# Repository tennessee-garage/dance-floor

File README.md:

# dance-floor
Code for various components of the LED disco dance floor

* [eagle](https://github.com/garthwebb/dance-floor/tree/master/eagle) - Eagle files for the PCBs used in this project
* [floor](https://github.com/garthwebb/dance-floor/tree/master/floor) - This code controls the light show on the dance floor
* poc_test - Proof of concept test code.
* [spi-buffer](https://github.com/garthwebb/dance-floor/tree/master/spi-buffer) - This code handles reading SPI weight data coming from the floor
* [square](https://github.com/garthwebb/dance-floor/tree/master/square) - This code run on the ATTiny in each square and manages the lights and weight sensors

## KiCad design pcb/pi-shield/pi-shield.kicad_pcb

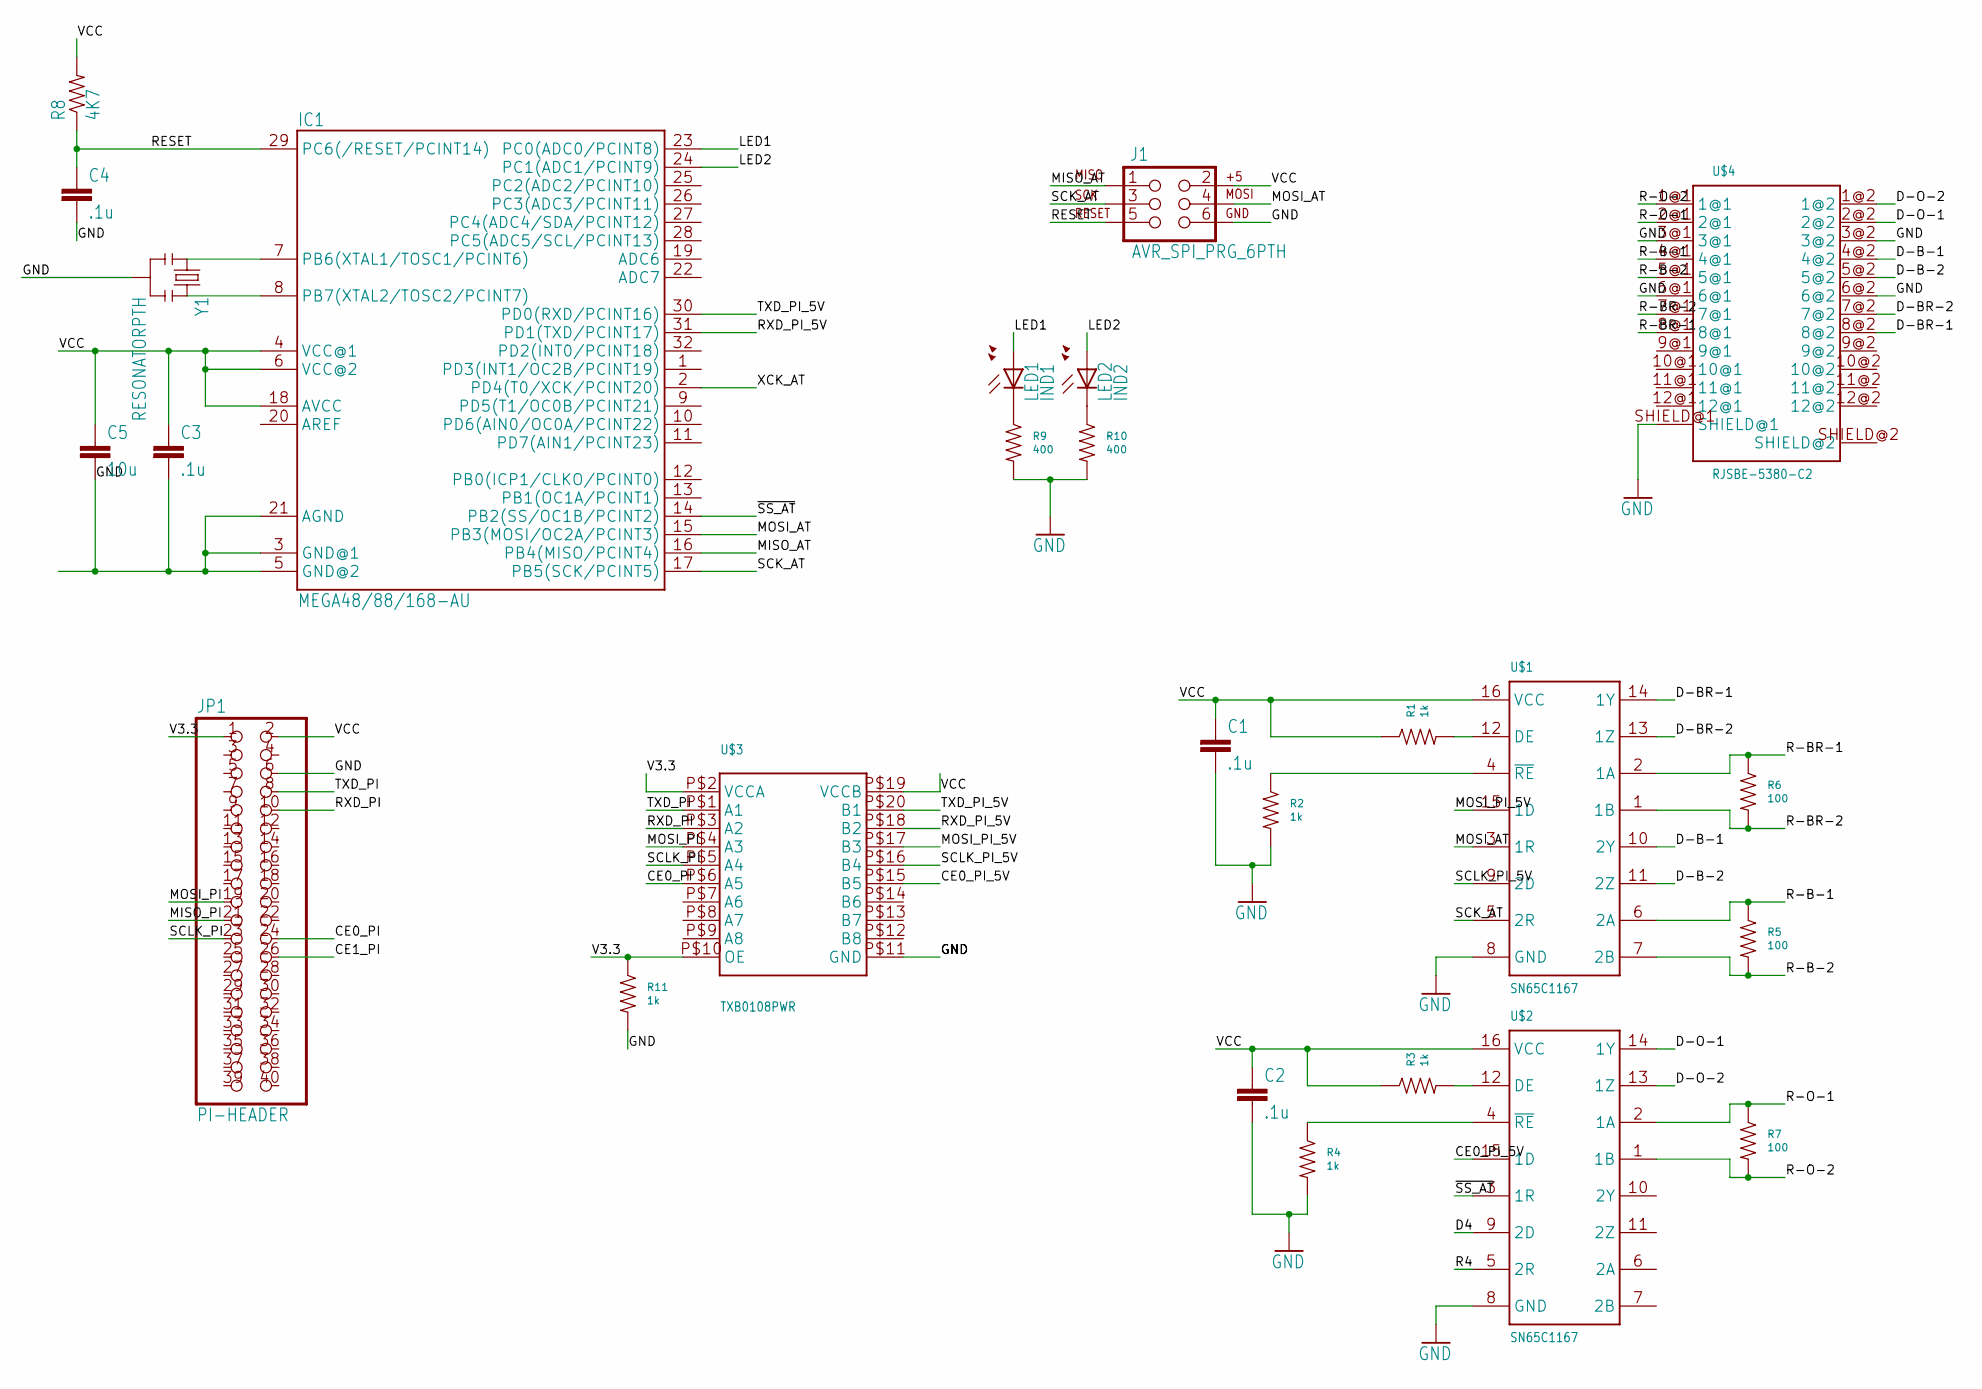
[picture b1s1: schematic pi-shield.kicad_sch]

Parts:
C1, C2, C3, C4: .1u; 0805
C5: 10u; 0805
IC1: MEGA48/88/168-AU; TQFP32-08
J1: AVR_SPI_PRG_6PTH; 2X3
JP1: PI-HEADER; 2X20
LED1: IND1; LED3MM
LED2: IND2; LED3MM
R1, R2, R3, R4, R11: 1k; R0805
R5, R6, R7: 100; R0805
R8: 4K7; 0805
R9, R10: 400; R0805
U$1, U$2: SN65C1167; SOP-16
U$3: TXB0108PWR; TSSOP20
U$4: RJSBE-5380-C2
Y1: RESONATORPTH; RESONATOR-PTH

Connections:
CE0_PI: JP1.24, U$3.P$6 (A5)
CE0_PI_5V: U$2.15 (1D), U$3.P$15 (B5)
CE1_PI: JP1.26
D4: U$2.9 (2D)
D-B-1: U$1.10 (2Y), U$4.4@2
D-B-2: U$1.11 (2Z), U$4.5@2
D-BR-1: U$1.14 (1Y), U$4.8@2
D-BR-2: U$1.13 (1Z), U$4.7@2
D-O-1: U$2.14 (1Y), U$4.2@2
D-O-2: U$2.13 (1Z), U$4.1@2
GND: C1.2, C2.2, C3.2, C4.2, C5.2, IC1.3 (GND@1), IC1.5 (GND@2), IC1.21 (AGND), J1.6, JP1.6, R2.P$2, R4.P$2, R9.P$2, R10.P$2, R11.P$2, U$1.8 (GND), U$2.8 (GND), U$3.P$11 (GND), U$4.3@1, U$4.3@2, U$4.6@1, U$4.6@2, U$4.SHIELD@1, Y1.2
LED1: IC1.23 (PC0(ADC0/PCINT8)), LED1.A
LED2: IC1.24 (PC1(ADC1/PCINT9)), LED2.A
MISO_AT: IC1.16 (PB4(MISO/PCINT4)), J1.1
MISO_PI: JP1.21
MOSI_AT: IC1.15 (PB3(MOSI/OC2A/PCINT3)), J1.4, U$1.3 (1R)
MOSI_PI: JP1.19, U$3.P$4 (A3)
MOSI_PI_5V: U$1.15 (1D), U$3.P$17 (B3)
unnamed: R1.P$2, U$1.12 (DE)
unnamed: R2.P$1, U$1.4 (~RE)
unnamed: R3.P$2, U$2.12 (DE)
unnamed: R4.P$1, U$2.4 (~RE)
unnamed: LED1.K (C), R9.P$1
unnamed: LED2.K (C), R10.P$1
unnamed: IC1.7 (PB6(XTAL1/TOSC1/PCINT6)), Y1.1
unnamed: IC1.8 (PB7(XTAL2/TOSC2/PCINT7)), Y1.3
R4: U$2.5 (2R)
R-B-1: R5.P$1, U$1.6 (2A), U$4.4@1
R-B-2: R5.P$2, U$1.7 (2B), U$4.5@1
R-BR-1: R6.P$1, U$1.2 (1A), U$4.8@1
R-BR-2: R6.P$2, U$1.1 (1B), U$4.7@1
R-O-1: R7.P$1, U$2.2 (1A), U$4.2@1
R-O-2: R7.P$2, U$2.1 (1B), U$4.1@1
RESET: C4.1, IC1.29 (PC6(/RESET/PCINT14)), J1.5, R8.1
RXD_PI: JP1.10, U$3.P$3 (A2)
RXD_PI_5V: IC1.31 (PD1(TXD/PCINT17)), U$3.P$18 (B2)
SCK_AT: IC1.17 (PB5(SCK/PCINT5)), J1.3, U$1.5 (2R)
SCLK_PI: JP1.23, U$3.P$5 (A4)
SCLK_PI_5V: U$1.9 (2D), U$3.P$16 (B4)
TXD_PI: JP1.8, U$3.P$1 (A1)
TXD_PI_5V: IC1.30 (PD0(RXD/PCINT16)), U$3.P$20 (B1)
V3.3: JP1.1, R11.P$1, U$3.P$2 (VCCA), U$3.P$10 (OE)
VCC: C1.1, C2.1, C3.1, C5.1, IC1.4 (VCC@1), IC1.6 (VCC@2), IC1.18 (AVCC), J1.2, JP1.2, R1.P$1, R3.P$1, R8.2, U$1.16 (VCC), U$2.16 (VCC), U$3.P$19 (VCCB)
XCK_AT: IC1.2 (PD4(T0/XCK/PCINT20))
~SS_AT: IC1.14 (PB2(SS/OC1B/PCINT2)), U$2.3 (1R)

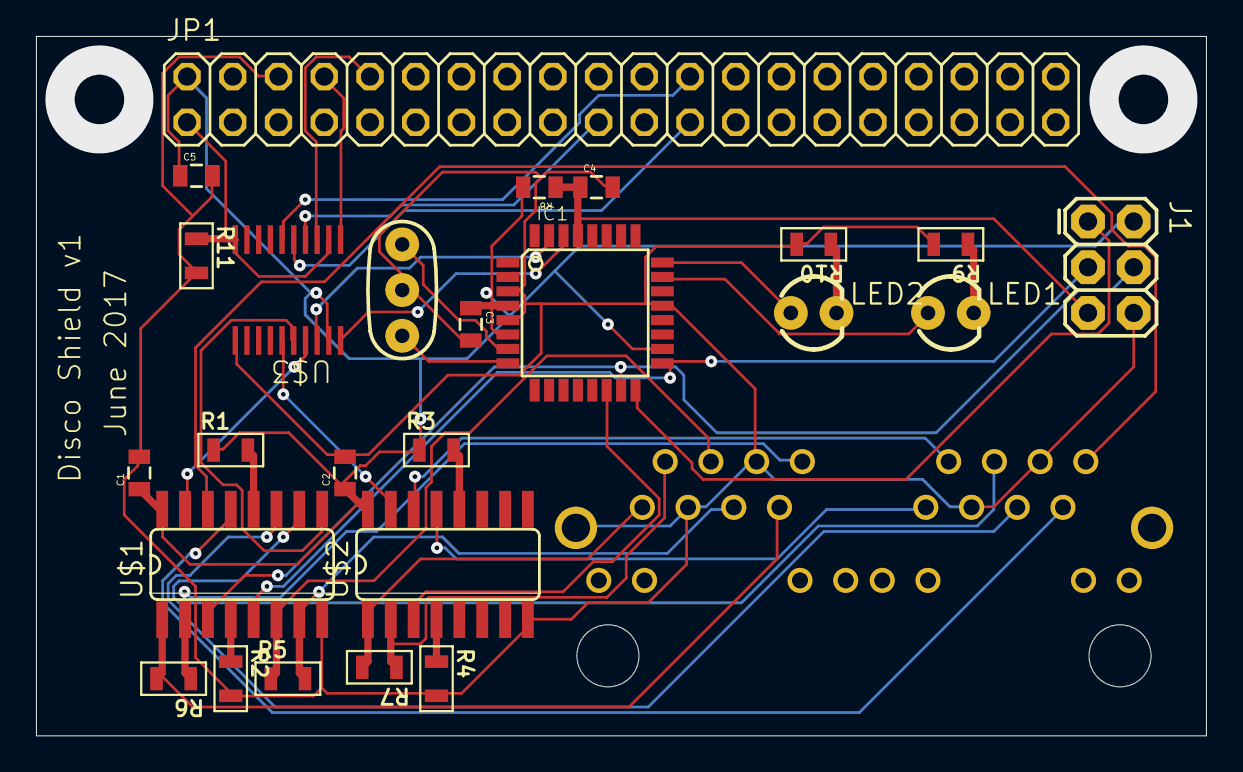
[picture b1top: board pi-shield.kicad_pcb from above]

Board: 2 copper layers, 65.0 x 38.9 mm, 26 parts (0 on the bottom side), 40 nets.

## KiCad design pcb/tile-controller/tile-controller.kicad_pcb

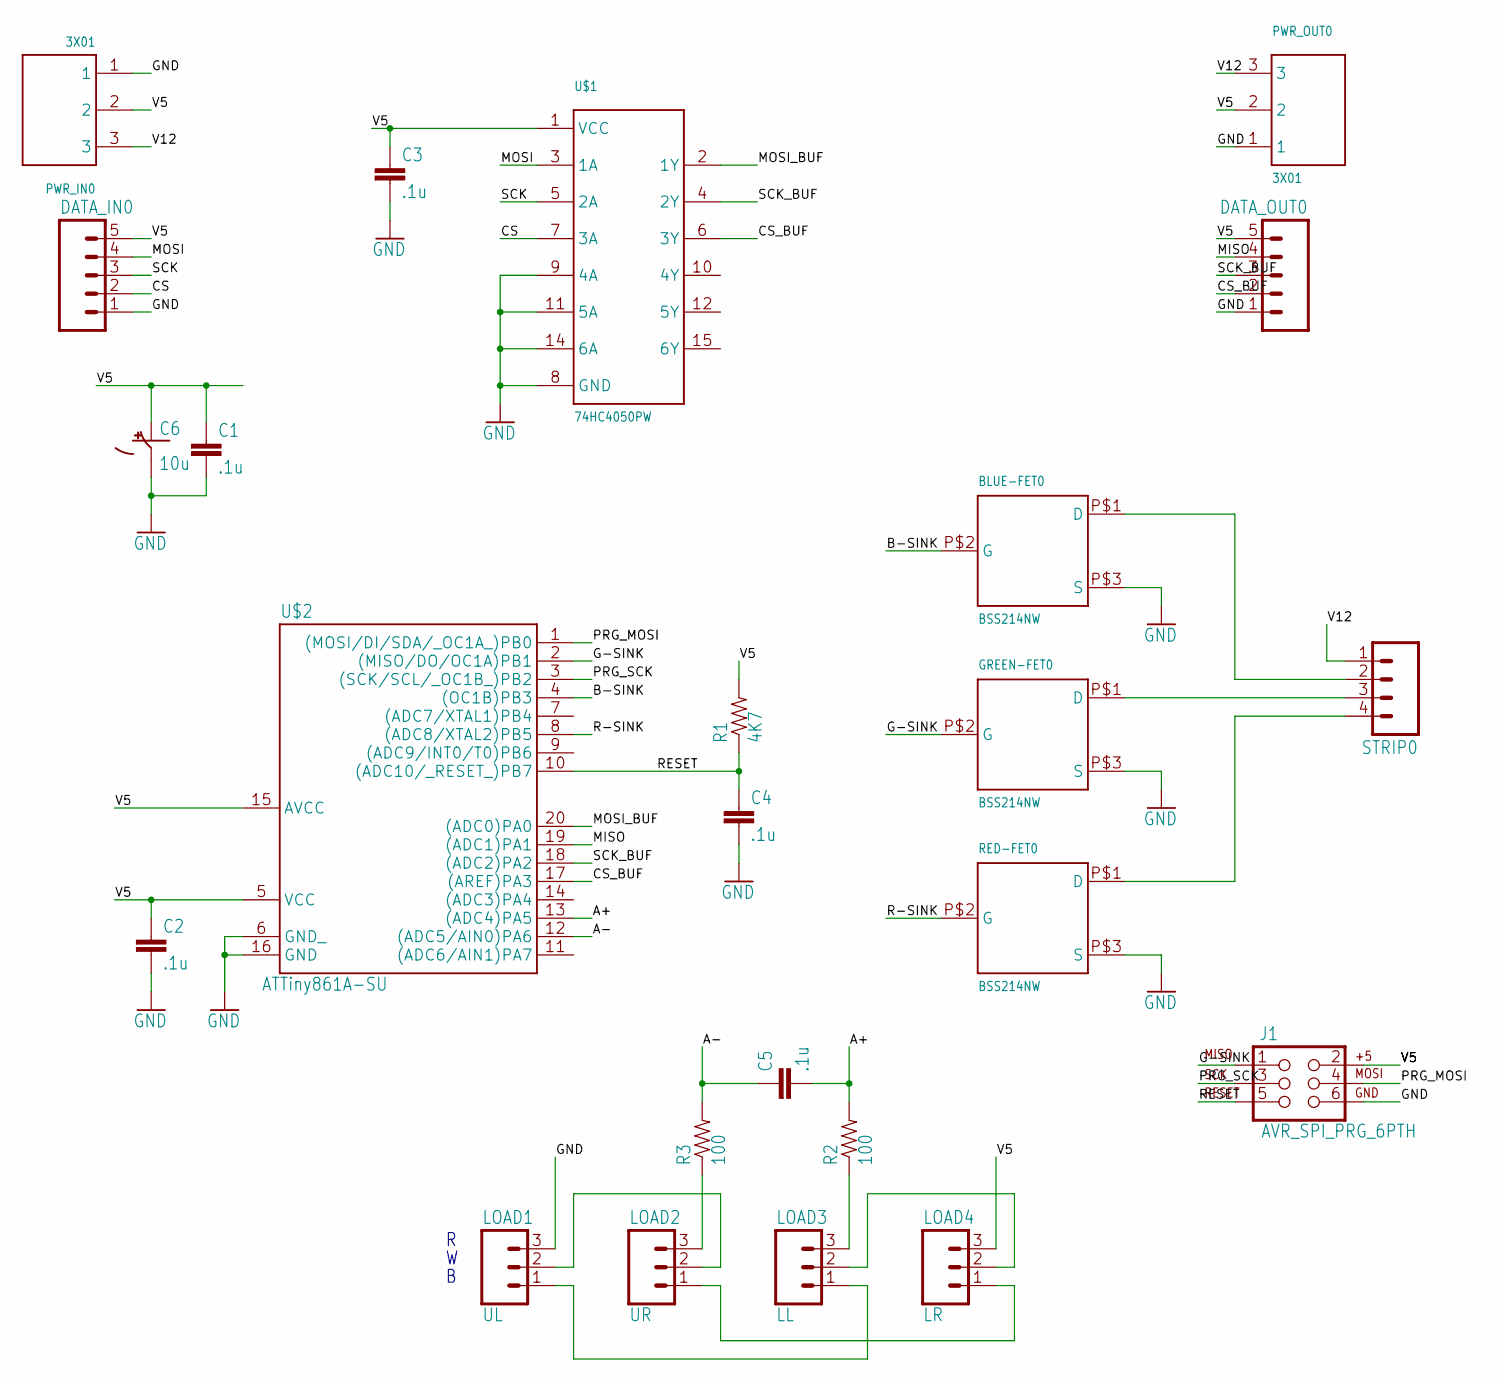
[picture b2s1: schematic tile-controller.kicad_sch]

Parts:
BLUE-FET0: BSS214NW; SOT-323
C1, C2, C3, C4, C5: .1u; 0805
C6: 10u; EIA3216
DATA_IN0: M05PTH; 1X05
DATA_OUT0: M05PTH; 1X05
GREEN-FET0: BSS214NW; SOT-323
J1: AVR_SPI_PRG_6PTH; 2X3
LOAD1: UL; 1X03
LOAD2: UR; 1X03
LOAD3: LL; 1X03
LOAD4: LR; 1X03
PWR_IN0: 3X01; 3X01-18AWG
PWR_OUT0: 3X01; 3X01-18AWG
R1: 4K7; 0805
R2, R3: 100; 0805
RED-FET0: BSS214NW; SOT-323
STRIP0: M04PTH; 1X04
U$1: 74HC4050PW; TSSOP16.2
U$2: ATTiny861A-SU; SO20L$

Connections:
A+: C5.2, R2.2, U$2.13 ((ADC4)PA5)
A-: C5.1, R3.2, U$2.12 ((ADC5/AIN0)PA6)
B-SINK: BLUE-FET0.P$2 (G), U$2.4 ((OC1B)PB3)
CS: DATA_IN0.2, U$1.7 (3A)
CS_BUF: DATA_OUT0.2, U$1.6 (3Y), U$2.17 ((AREF)PA3)
G-SINK: GREEN-FET0.P$2 (G), J1.1, U$2.2 ((MISO/DO/OC1A)PB1)
GND: BLUE-FET0.P$3 (S), C1.2, C2.2, C3.2, C4.2, C6.C (-), DATA_IN0.1, DATA_OUT0.1, GREEN-FET0.P$3 (S), J1.6, LOAD1.3, PWR_IN0.1, PWR_OUT0.1, RED-FET0.P$3 (S), U$1.8 (GND), U$1.9 (4A), U$1.11 (5A), U$1.14 (6A), U$2.6 (GND_), U$2.16 (GND)
MISO: DATA_OUT0.4, U$2.19 ((ADC1)PA1)
MOSI: DATA_IN0.4, U$1.3 (1A)
MOSI_BUF: U$1.2 (1Y), U$2.20 ((ADC0)PA0)
unnamed: LOAD1.1, LOAD3.1
unnamed: LOAD2.1, LOAD4.1
unnamed: GREEN-FET0.P$1 (D), STRIP0.3
unnamed: BLUE-FET0.P$1 (D), STRIP0.2
unnamed: RED-FET0.P$1 (D), STRIP0.4
unnamed: LOAD1.2, LOAD2.2
unnamed: LOAD3.2, LOAD4.2
PRG_MOSI: J1.4, U$2.1 ((MOSI/DI/SDA/_OC1A_)PB0)
PRG_SCK: J1.3, U$2.3 ((SCK/SCL/_OC1B_)PB2)
R-SINK: RED-FET0.P$2 (G), U$2.8 ((ADC8/XTAL2)PB5)
RESET: C4.1, J1.5, R1.1, U$2.10 ((ADC10/_RESET_)PB7)
SCK: DATA_IN0.3, U$1.5 (2A)
SCK_BUF: DATA_OUT0.3, U$1.4 (2Y), U$2.18 ((ADC2)PA2)
V5: C1.1, C2.1, C3.1, C6.A (+), DATA_IN0.5, DATA_OUT0.5, J1.2, LOAD4.3, PWR_IN0.2, PWR_OUT0.2, R1.2, U$1.1 (VCC), U$2.5 (VCC), U$2.15 (AVCC)
V12: PWR_IN0.3, PWR_OUT0.3, STRIP0.1
_1: LOAD2.3, R3.1
_2: LOAD3.3, R2.1

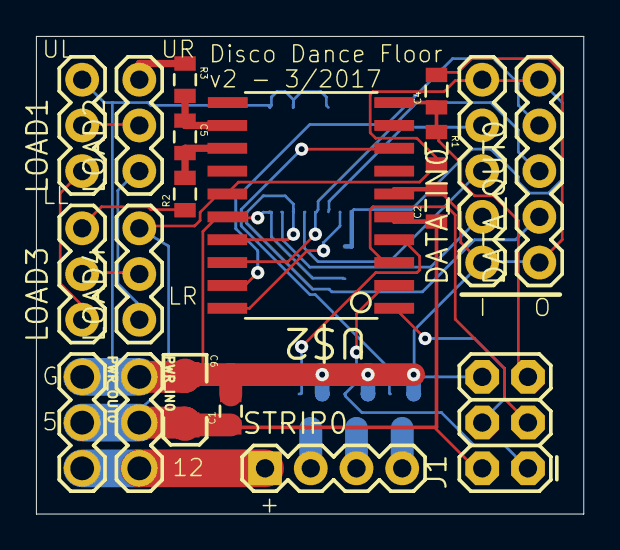
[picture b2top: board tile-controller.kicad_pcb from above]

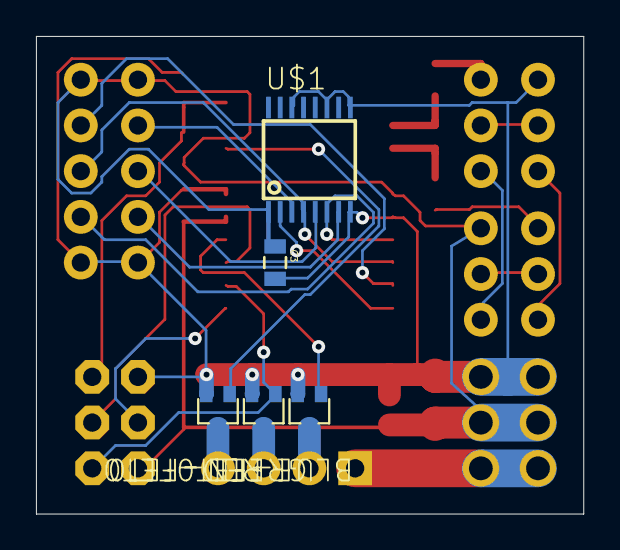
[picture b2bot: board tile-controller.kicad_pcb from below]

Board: 2 copper layers, 30.4 x 26.5 mm, 24 parts (5 on the bottom side), 27 nets.

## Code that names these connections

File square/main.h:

#ifndef _MAIN_H
#define _MAIN_H

#define SET_PA0() SET_PIN(PORTA, PA0)
#define SET_PA1() SET_PIN(PORTA, PA1)
#define SET_PA2() SET_PIN(PORTA, PA2)
#define SET_PA3() SET_PIN(PORTA, PA3)
#define SET_PA4() SET_PIN(PORTA, PA4)
#define SET_PA5() SET_PIN(PORTA, PA5)
#define SET_PA6() SET_PIN(PORTA, PA6)
#define SET_PA7() SET_PIN(PORTA, PA7)
#define CLEAR_PA0() CLEAR_PIN(PORTA, PA0)
#define CLEAR_PA1() CLEAR_PIN(PORTA, PA1)
#define CLEAR_PA2() CLEAR_PIN(PORTA, PA2)
#define CLEAR_PA3() CLEAR_PIN(PORTA, PA3)
#define CLEAR_PA4() CLEAR_PIN(PORTA, PA4)
#define CLEAR_PA5() CLEAR_PIN(PORTA, PA5)
#define CLEAR_PA6() CLEAR_PIN(PORTA, PA6)
#define CLEAR_PA7() CLEAR_PIN(PORTA, PA7)

#define SET_PB0() SET_PIN(PORTB, PB0)
#define SET_PB1() SET_PIN(PORTB, PB1)
#define SET_PB2() SET_PIN(PORTB, PB2)
#define SET_PB3() SET_PIN(PORTB, PB3)
#define SET_PB4() SET_PIN(PORTB, PB4)
#define SET_PB5() SET_PIN(PORTB, PB5)
#define SET_PB6() SET_PIN(PORTB, PB6)
#define SET_PB7() SET_PIN(PORTB, PB7)
#define CLEAR_PB0() CLEAR_PIN(PORTB, PB0)
#define CLEAR_PB1() CLEAR_PIN(PORTB, PB1)
#define CLEAR_PB2() CLEAR_PIN(PORTB, PB2)
#define CLEAR_PB3() CLEAR_PIN(PORTB, PB3)
#define CLEAR_PB4() CLEAR_PIN(PORTB, PB4)
#define CLEAR_PB5() CLEAR_PIN(PORTB, PB5)
#define CLEAR_PB6() CLEAR_PIN(PORTB, PB6)
#define CLEAR_PB7() CLEAR_PIN(PORTB, PB7)

#define SET_PIN(port, pin) port |= _BV(pin)
#define CLEAR_PIN(port, pin) port &= ~_BV(pin)

void init_avr(void);
void init_pwm(void);
void init_adc(void);
void set_red(uint16_t val);
void set_green(uint16_t val);
void set_blue(uint16_t val);
void handle_spi(void);
void handle_adc(void);
int main(void);

#endif

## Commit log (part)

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2017-02-03 More ignored files
2017-02-03 Code to measure differential ADC and light the lights according to the result
2017-02-26 Got i2c working (but buggy) and cleaned up code a bit
2017-03-28 A bit more clean up
2017-04-03 Storing all bytes in a long buffer. Considered using a 4 byte FIFO but keeping everying in one array is much simpler and the space is available.
2017-05-30 Start of the code for the SPI buffer
2017-05-31 Don't make this complicated
2017-06-01 Test program
2017-06-04 Get rid of *.pyc files from commits
2017-06-05 Added a message file that will be read, with default. Added color cycling
2017-06-05 add multiple sources, tweak decay time
2017-06-06 code cleanup
2017-06-08 add x,y args to build_mine
2017-06-10 Renamed the effect
2017-06-11 Updates to add keyboard input for weight values. Default is on. Can be turned off via:
    --no-opc-input
2017-06-12 Ignore DS_Store files
2017-06-12 Two new screenshots
2017-06-18 Additional board
2017-07-05 Don't track lock files
2017-07-09 Don't need to follow the OPC quickstart guide
2017-07-09 function to translate (x,y) coords to array index
2017-07-09 drop debug prints
2017-07-09 typo
2017-07-10 Added the radiating animation
2017-07-10 Unify the color functions in color_tools to the color_utils file
2017-07-10 Updated for PEP8
2017-07-20 Got the spi buffer streaming data via the USART
2017-07-20 use color_utils
2017-07-23 floor: devserver: simple support for weights onClick.
2017-07-23 floor: deserver: bugfix: handle non-integer rgb values.
2017-07-23 controller: bugfix.
2017-07-23 Initial API service.
2017-07-23 controller: support reloading processor modules.
2017-07-24 api: support `POST /api/bpm/nudge` (relative changes to bpm/downbeat).
2017-07-24 api: add `/api/status`, composite playlist and tempo info.
2017-07-25 Hyperspace
    added hyperspace processor, also added fishies and hyperspace to the playlist and added a color to rainbow_bunny
2017-07-27 Output the driver name and its max led value on start up
2017-07-28 Update the SPI buffer to only send the two bytes of weight information, rather than pass along the full four bytes it gets from the floor.
    Two of the four bytes will always be zero, so there's no need to transmit them. Since the two bytes represent a
    10-bit value, only 10 of the 16 bits in those two bytes are used, so we still have a valid stop condition (0xFF, 0xFF)
    Finally, handle serial synchronously rather than running a thread. Running a thread seemed to cause problems and made things more
    complex to program and debug. Its main goal was to make sure we weren't blocked on IO when we could be rendering a frame but that
    doesn't seem to be an issue.
2017-07-28 Some updates to deprecate OPC
2017-07-28 Add a time remaining indicator
2017-07-30 Make some improvements to electricity, though still not operating as well as I'd like
    Also make sure we don't get a warning when starting stripes
2017-07-30 api: add available processors to status API; docs.
2017-07-30 Add throbber to default playlist.
2017-08-03 api: add `POST /api/playlist/previous` to go back.
2017-08-05 Add "zap" to default playlist.
2017-10-15 Removed most references to the opc driver
    The OPC driver has been superseded by the devserver which is way better.
2018-04-26 Test with normal ADC and no odd off by 3 first frame from SPI
    Got this all working. Checkpointing
2018-08-26 Don't call data_ready as if its a function
2018-08-26 Refactor JS and CSS out a bit. Create page container
2018-08-26 Make sure the server doesn't die if the floor is powered on after the server is running.
2018-08-31 Add pipenv.
2018-09-17 tests: add unittest for the `clocked` decorator.
2018-09-18 Update to latest pymidi.
2018-09-18 Committing change to this file though it was probably just a perspective change /shrug
2018-09-20 midi: improve mapping support; add passthrough; add tests.
2018-09-21 Updated the playlist and added an alias for run show
2018-09-30 Append takes no args
2018-09-30 Update imports across project.
    * Add floor. to imports where necessary
    * Change ordering of imports to list global imports first, project local second.
    * Fix any PEP warnings
2018-10-01 Ok, default isn't a key
2018-10-01 Use an absolute path for the playlist.
    Otherwise where you start the script matters
2018-10-01 Fix dynamic import
2018-10-14 Allow patterns to set their own FPS.
    Update the ripple pattern to set 120 FPS.
2018-10-19 Simple scripts to set a single square red green or blue.
    Useful for testing dead squares, or squares where two colors are connected
2018-10-22 floor: require python 2
2018-12-23 Add the ability to set MIDI mapping files
    * Created new midi_maps directory
    * Created JSON file for the AKAI APCmini
    * Updated MidiManager to read from files
    * Added --midi_mapping arg to run_show
    * Mapped start, stop, stay, forward, back, bpm and brightness global MIDI functions
    * Updated 'ripple' processor to respond to MIDI commands (hardcoded to APC mini config)
2018-12-24 Add mapping for APCMini 8x8 pads to dance floor foot presses
2018-12-25 floor: use `flask-sockets` for websocket library
2018-12-26 floor: add Build Status to README.
2018-12-26 A version of spiral that is locked to 1 frame per beat.
    Not really part of the foot responsive patterns but wanted to get this checked in as its been floating here for a while
2018-12-27 processors: use `context.clock` instead of `time.time()`.
    Making processors use our own clock means:
    * Processors are insensitive to drift or changes in “wall time”.
    * Clock can easily be injected for testing and/or profiling.
    * Clock can be artificially sped up or slowed down, e.g. to achieve a faster/slower rendering effect.
    It also means fewer syscalls during execution, e.g. only one call
    site fetching system time, but that’s likely a micro-optimization.
2018-12-27 Typo!
2018-12-27 Fix tests after recent updates to midi functions
2018-12-28 Clean up some no longer needed code
2018-12-29 Step one in getting the plumbing right before updating processors
2018-12-29 Add processor benchmark script.
    Example usage:
    ```
    $ python bin/benchmark.py Ripple
    INFO: Setting bpm to: 120.0
    INFO: Starting benchmark of Ripple with 100000 iterations ...
    INFO: Advanced to: Ripple (position=0)
2018-12-31 First test of live speed profiling
2019-01-21 processor: don’t register the `Base` class in the registry.
2019-01-21 processor: remove explicit `set_bpm()` callback.
    It turns out no current processor needed the callback, so this
    change opportunistically simplifies/reduces the affected interfaces.
2019-01-21 devserver: restore handling of weight clicks.
    Closes #7.
2019-01-21 controller: introduce rendering layers.
2019-01-21 utils: rename method (pr discussion).
2019-01-21 processor: Show a more helpful message upon name clash.
2019-01-21 clocked: pull up a calculation (pr feedback)
2019-01-21 Add an annotation based profiler that gets out of the way when not needed.
2019-03-17 py2to3: add `future` package
2019-04-06 py2to3: manual fixes
2019-05-19 Update python dependencies.
    Automated result of: `pipenv update`
    Closes a security alert with Jinja
    (https://nvd.nist.gov/vuln/detail/CVE-2019-10906)
2019-05-23 Fix typo.
2019-06-08 cleanup: rearrange class order; no changes to functionality.
    Since `PlaylistRenderLayer` is now implemented in terms of an internal
    `ProcessorRenderLayer`, its more intuitive to declare the more basic
    class first.
2019-06-08 ChaChaCha: example use of wet/dry fader to change pallets
2019-06-08 include ranged values and switches in RenderContext
2019-09-02 Added a new layout for single pod testing.
    This cascaded in a few other depenent fixes/cleanups
2019-09-04 Add some labels for the slider controls
    Starting with tooltips
2019-09-05 Fix `black_is_alpha` behavior broken in #54
2019-09-14 Support multiple drivers.
2019-09-20 playlist: refactor `from_file` impl
2019-09-24 Update the docs to include an npm install and a path change
2019-09-26 Add a timeout for the floor probe.
    This is needed for when the floor is not actually attached to the Pi (testing etc), or not currently powered up. In these cases the probe will hang forever waiting for packets to return. In this case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
    There's probably a better way to do this timeout (lib, etc) but opting for a zero dependency increase for this commit so that I can safely use it this weekend and not be debugging this small detail.
    This has been tested on the Pi and the time out works.
2021-03-20 build(deps): bump jinja2 from 2.10.1 to 2.11.3 in /floor
    Bumps [jinja2](https://github.com/pallets/jinja) from 2.10.1 to 2.11.3.
    - [Release notes](https://github.com/pallets/jinja/releases)
    - [Changelog](https://github.com/pallets/jinja/blob/master/CHANGES.rst)
    - [Commits](https://github.com/pallets/jinja/compare/2.10.1...2.11.3)
2023-07-09 floor: replace deprecated websocket library
2023-07-09 floor: run `black` and `isort` everywhere, for consistent style
    command used: `pre-commit run --all`
2025-04-23 Comitting the codebase as found on the production RaspberryPi
    It was running an OS that was too old to load a recent version of git. Most of the changes seem to be linting types of changes. Going to start fresh, but keep this copy here just incase there was any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
2025-04-24 Update README.md
    Oh jesus christ, ' poetry env activate' only prints the commend to use to activate the environment, it doesn't actually run it. What an extremely fussy implementation.
2025-04-25 Looks like the formatting might have been linted out into something less readable. Lets pack it back up
2025-04-26 Change the eagle directory to more general "pcb"
2025-04-26 Adding updated files for the pi-shield in KiCad
2025-04-26 Clear the USI counter after chip select goes low
    Very hopeful this will fix the instability issues with the tile. When the floor gets in this state it seems like its not shifting data along the 4 byte boundary for each square. My theory is that the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
    By clearing the USI counter after select goes high, regardless of what we read in, it should guaruntee that we're in a good, known state to accept new data.
2025-04-26 Added STL versions of all the files
2025-04-29 Commit the last version of the platformio.ini file I used
2025-04-30 Checkpointing work so far on an interrupt version.
    Still not working, doesn't seem worth the effort. Going back to a tight loop
2025-04-30 Added in a check for the chip select before continuing
    Combined with clearing the USI counter, ideally this keeps us from getting into an inconsistent state
2025-08-28 Upodate with some fixes found in testing with the floor.
2025-09-05 floor: switch to ruff for python linting/formatting, part 1
    - perform all automatic/safe fixes
2025-09-05 floor: fix up build scripts
